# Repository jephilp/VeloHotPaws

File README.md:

# VeloHotPaws
Michigan Tech's Velovation Enterprise Hot Paws Repo

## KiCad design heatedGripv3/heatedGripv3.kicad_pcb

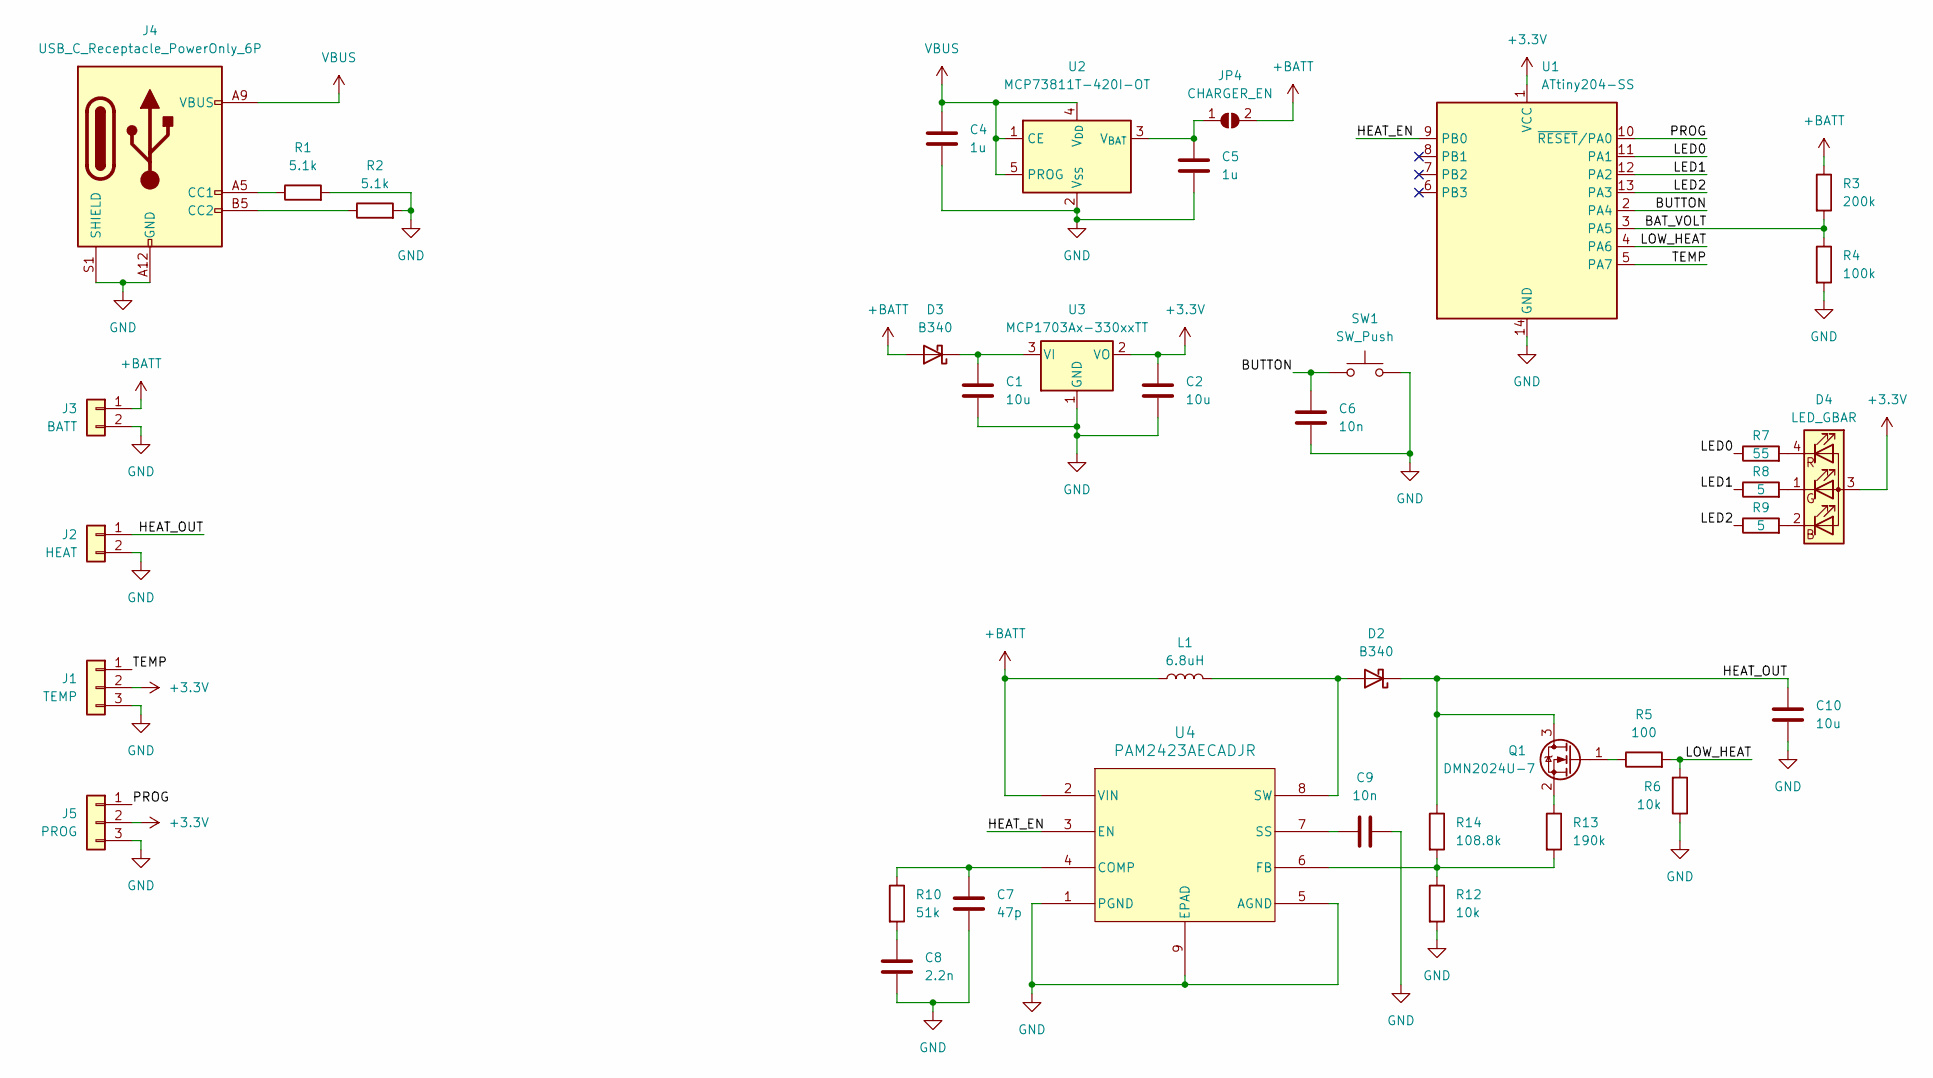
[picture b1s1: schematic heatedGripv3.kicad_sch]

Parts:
C1, C2, C10: 10u; C_0603_1608Metric_Pad1.08x0.95mm_HandSolder
C4, C5: 1u; C_0603_1608Metric_Pad1.08x0.95mm_HandSolder
C6, C9: 10n; C_0603_1608Metric_Pad1.08x0.95mm_HandSolder
C7: 47p; C_0603_1608Metric_Pad1.08x0.95mm_HandSolder
C8: 2.2n; C_0603_1608Metric_Pad1.08x0.95mm_HandSolder
D2, D3: B340; D_SMA
D4: LED_GBAR; LED_D5.0mm-4_RGB_Wide_Pins
J1: TEMP; PinHeader_1x03_P2.54mm_Vertical
J2: HEAT; PinHeader_1x02_P2.54mm_Horizontal
J3: BATT; PinHeader_1x02_P2.54mm_Horizontal
J4: USB_C_Receptacle_PowerOnly_6P; USB_C_Receptacle_GCT_USB4135-GF-A_6P_TopMnt_Horizontal
J5: PROG; PinHeader_1x03_P2.54mm_Vertical
JP4: CHARGER_EN; SolderJumper-2_P1.3mm_Open_Pad1.0x1.5mm
L1: 6.8uH; L_Bourns_SRP1038C_10.0x10.0mm
Q1: DMN2024U-7; SOT-23
R1, R2: 5.1k; R_0603_1608Metric_Pad0.98x0.95mm_HandSolder
R3: 200k; R_0603_1608Metric_Pad0.98x0.95mm_HandSolder
R4: 100k; R_0603_1608Metric_Pad0.98x0.95mm_HandSolder
R5: 100; R_0603_1608Metric_Pad0.98x0.95mm_HandSolder
R6, R12: 10k; R_0603_1608Metric_Pad0.98x0.95mm_HandSolder
R7: 55; R_0603_1608Metric_Pad0.98x0.95mm_HandSolder
R8, R9: 5; R_0603_1608Metric_Pad0.98x0.95mm_HandSolder
R10: 51k; R_0603_1608Metric_Pad0.98x0.95mm_HandSolder
R13: 190k; R_0603_1608Metric_Pad0.98x0.95mm_HandSolder
R14: 108.8k; R_0603_1608Metric_Pad0.98x0.95mm_HandSolder
SW1: SW_Push; SW_SPST_EVQP7C
U1: ATtiny204-SS; SOIC-14_3.9x8.7mm_P1.27mm
U2: MCP73811T-420I-OT; SOT-23-5
U3: MCP1703Ax-330xxTT; SOT-23
U4: PAM2423AECADJR; SOIC-8-1EP_3.9x4.9mm_P1.27mm_EP2.29x3mm

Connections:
+3.3V: C2.1, D4.3 (A), J1.2, J5.2, U1.1 (VCC), U3.2 (VO)
+BATT: D3.2 (A), J3.1, JP4.2 (B), L1.1, R3.1, U4.2 (VIN)
/BAT_VOLT: R3.2, R4.1, U1.3 (PA5)
/BUTTON: C6.2, SW1.1, U1.2 (PA4)
/HEAT_EN: U1.9 (PB0), U4.3 (EN)
/HEAT_OUT: C10.1, D2.1 (K), J2.1, Q1.3 (D), R14.1
/LED0: R7.1, U1.11 (PA1)
/LED1: R8.1, U1.12 (PA2)
/LED2: R9.1, U1.13 (PA3)
/LOW_HEAT: R5.2, R6.2, U1.4 (PA6)
/PROG: J5.1, U1.10 (~RESET/PA0)
/TEMP: J1.1, U1.5 (PA7)
GND: C1.2, C2.2, C4.2, C5.2, C6.1, C7.2, C8.2, C9.2, C10.2, J1.3, J2.2, J3.2, J4.A12 (GND), J4.B12 (GND), J4.S1 (SHIELD), J5.3, R1.2, R2.2, R4.2, R6.1, R12.2, SW1.2, U1.14 (GND), U2.2 (V_{SS}), U3.1 (GND), U4.1 (PGND), U4.5 (AGND), U4.9 (EPAD)
unnamed: C8.1, R10.2
unnamed: D2.2 (A), L1.2, U4.8 (SW)
unnamed: C1.1, D3.1 (K), U3.3 (VI)
unnamed: D4.2 (BK), R9.2
unnamed: D4.1 (GK), R8.2
unnamed: D4.4 (RK), R7.2
unnamed: J4.A5 (CC1), R1.1
unnamed: J4.B5 (CC2), R2.1
unnamed: C5.1, JP4.1 (A), U2.3 (V_{BAT})
unnamed: Q1.1 (G), R5.1
unnamed: Q1.2 (S), R13.1
unnamed: C7.1, R10.1, U4.4 (COMP)
unnamed: R12.1, R13.2, R14.2, U4.6 (FB)
unnamed: C9.1, U4.7 (SS)
VBUS: C4.1, J4.A9 (VBUS), J4.B9 (VBUS), U2.1 (CE), U2.4 (V_{DD}), U2.5 (PROG)

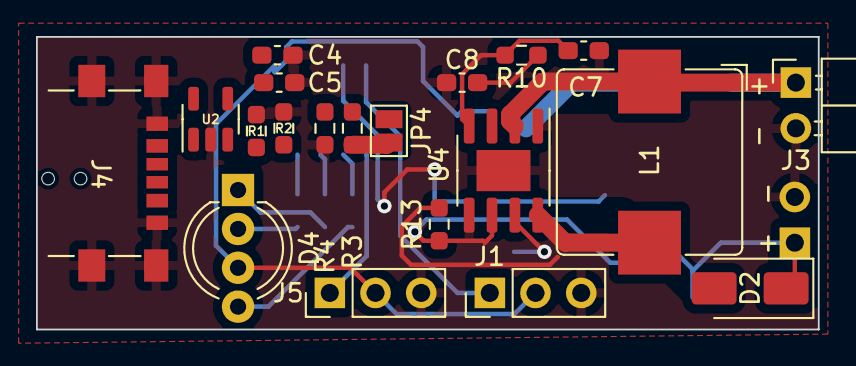
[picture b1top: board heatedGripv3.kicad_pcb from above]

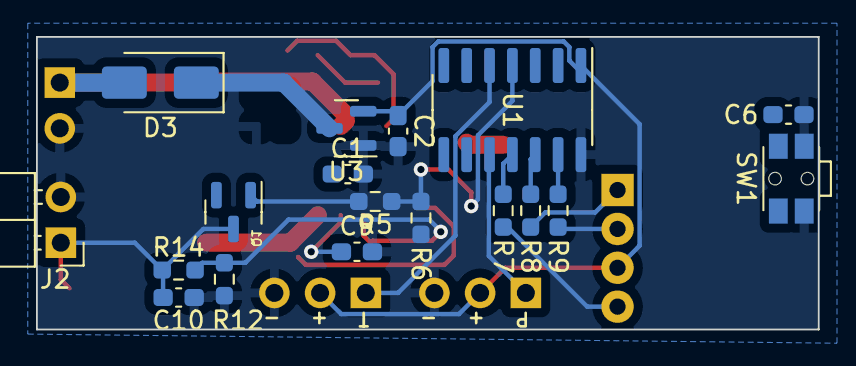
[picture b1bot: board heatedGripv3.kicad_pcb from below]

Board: 2 copper layers, 43.4 x 16.3 mm, 38 parts (18 on the bottom side), 28 nets.

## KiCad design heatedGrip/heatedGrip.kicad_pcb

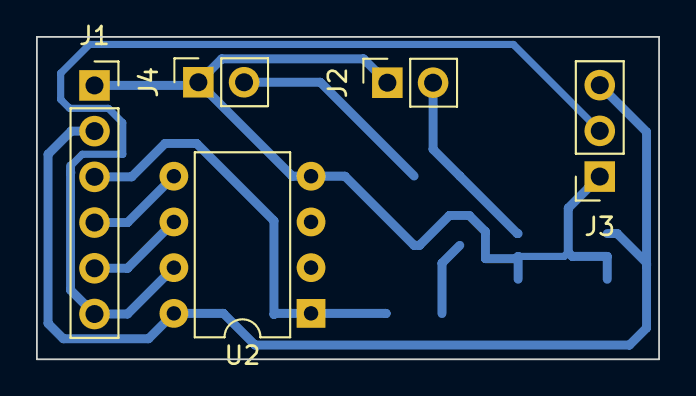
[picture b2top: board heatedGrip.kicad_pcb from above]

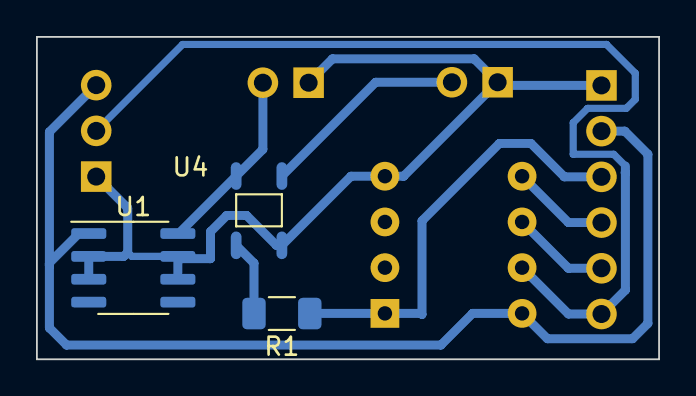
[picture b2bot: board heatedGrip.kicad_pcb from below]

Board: 2 copper layers, 34.6 x 17.9 mm, 8 parts (3 on the bottom side), 9 nets.

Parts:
J1: Conn_01x06_Female; PinSocket_1x06_P2.54mm_Vertical
J2, J4: Conn_01x02_Female; PinSocket_1x02_P2.54mm_Vertical
J3: Conn_01x03_Female; PinSocket_1x03_P2.54mm_Vertical
R1: 100; R_1206_3216Metric_Pad1.30x1.75mm_HandSolder
U1: L78L05_SO8; SOIC-8_3.9x4.9mm_P1.27mm
U2: ATtiny25-20P; DIP-8_W7.62mm
U4: CPC1020N

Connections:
+5V: J1.2, J3.3, U1.1 (OUT), U2.8 (VCC)
+7.5V: J2.2, U1.8 (IN), U4.4 (Load)
GND: J1.1, J2.1, J3.1, J4.1, U1.2 (GND), U1.3 (GND), U1.6 (GND), U1.7 (GND), U2.4 (GND), U4.2 (-_Control)
unnamed: J1.3, R1.1, U2.1 (~RESET/PB5)
unnamed: J1.4, U2.5 (AREF/PB0)
unnamed: J1.5, U2.6 (PB1)
unnamed: R1.2, U4.1 (+_Control)
unnamed: J4.2, U4.3 (Load)
Sens: J1.6, J3.2, U2.7 (PB2)

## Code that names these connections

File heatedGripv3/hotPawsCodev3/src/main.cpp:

#include <Arduino.h>

#define HEATON PIN_PB0
// Red
#define LED0 PIN_PA1
// Blue
#define LED1 PIN_PA2
// Green
#define LED2 PIN_PA3
#define BUTTON PIN_PA4
#define VOLTAGE PIN_PA5
#define LOWHEAT PIN_PA6
#define TEMP PIN_PA7

void buttonPress();

void setup() {
  // put your setup code here, to run once:
  analogReference(INTERNAL2V5);
  analogReadResolution(10);
  pinMode(HEATON, OUTPUT);
  digitalWrite(HEATON, LOW);
  pinMode(LED0, OUTPUT);
  pinMode(LED1, OUTPUT);
  pinMode(LED2, OUTPUT);
  digitalWrite(LED0, HIGH);
  digitalWrite(LED1, HIGH);
  digitalWrite(LED2, HIGH);
  pinMode(BUTTON, INPUT_PULLUP);
  pinMode(VOLTAGE, INPUT);
  pinMode(LOWHEAT, OUTPUT);
  digitalWrite(LOWHEAT, HIGH);
  pinMode(TEMP, INPUT);
  //attachInterrupt(BUTTON, buttonPress, RISING);
}
bool ledON = false;
float voltage = 0;
float realTemp = 0;
float targetTemp = 45;
void loop() {

//digitalWrite(HEATON, LOW);
//digitalWrite(LED0, LOW);
delay(200);
digitalWrite(HEATON, HIGH);
digitalWrite(LED0, HIGH);
digitalWrite(LOWHEAT, HIGH);
//voltage = 2.5f*(analogRead(TEMP)/1023.0);
//realTemp = 100.0*(voltage-0.5);

/*
  if(realTemp >= targetTemp){
    digitalWrite(HEATON, LOW);
    digitalWrite(LOWHEAT, LOW);
    digitalWrite(LED0, HIGH);
  }else{
    digitalWrite(LED0, LOW);
    digitalWrite(HEATON, HIGH);
    digitalWrite(LOWHEAT, HIGH);
  }
  */
delay(5000);
}

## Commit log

2022-11-16 Added board files and code
2023-09-06 Added new board
2023-09-12 Updated
    Added extra ports and reviewed
2023-09-12 Added Prod
2024-02-23 Added v3
2024-02-23 Small tweaks
